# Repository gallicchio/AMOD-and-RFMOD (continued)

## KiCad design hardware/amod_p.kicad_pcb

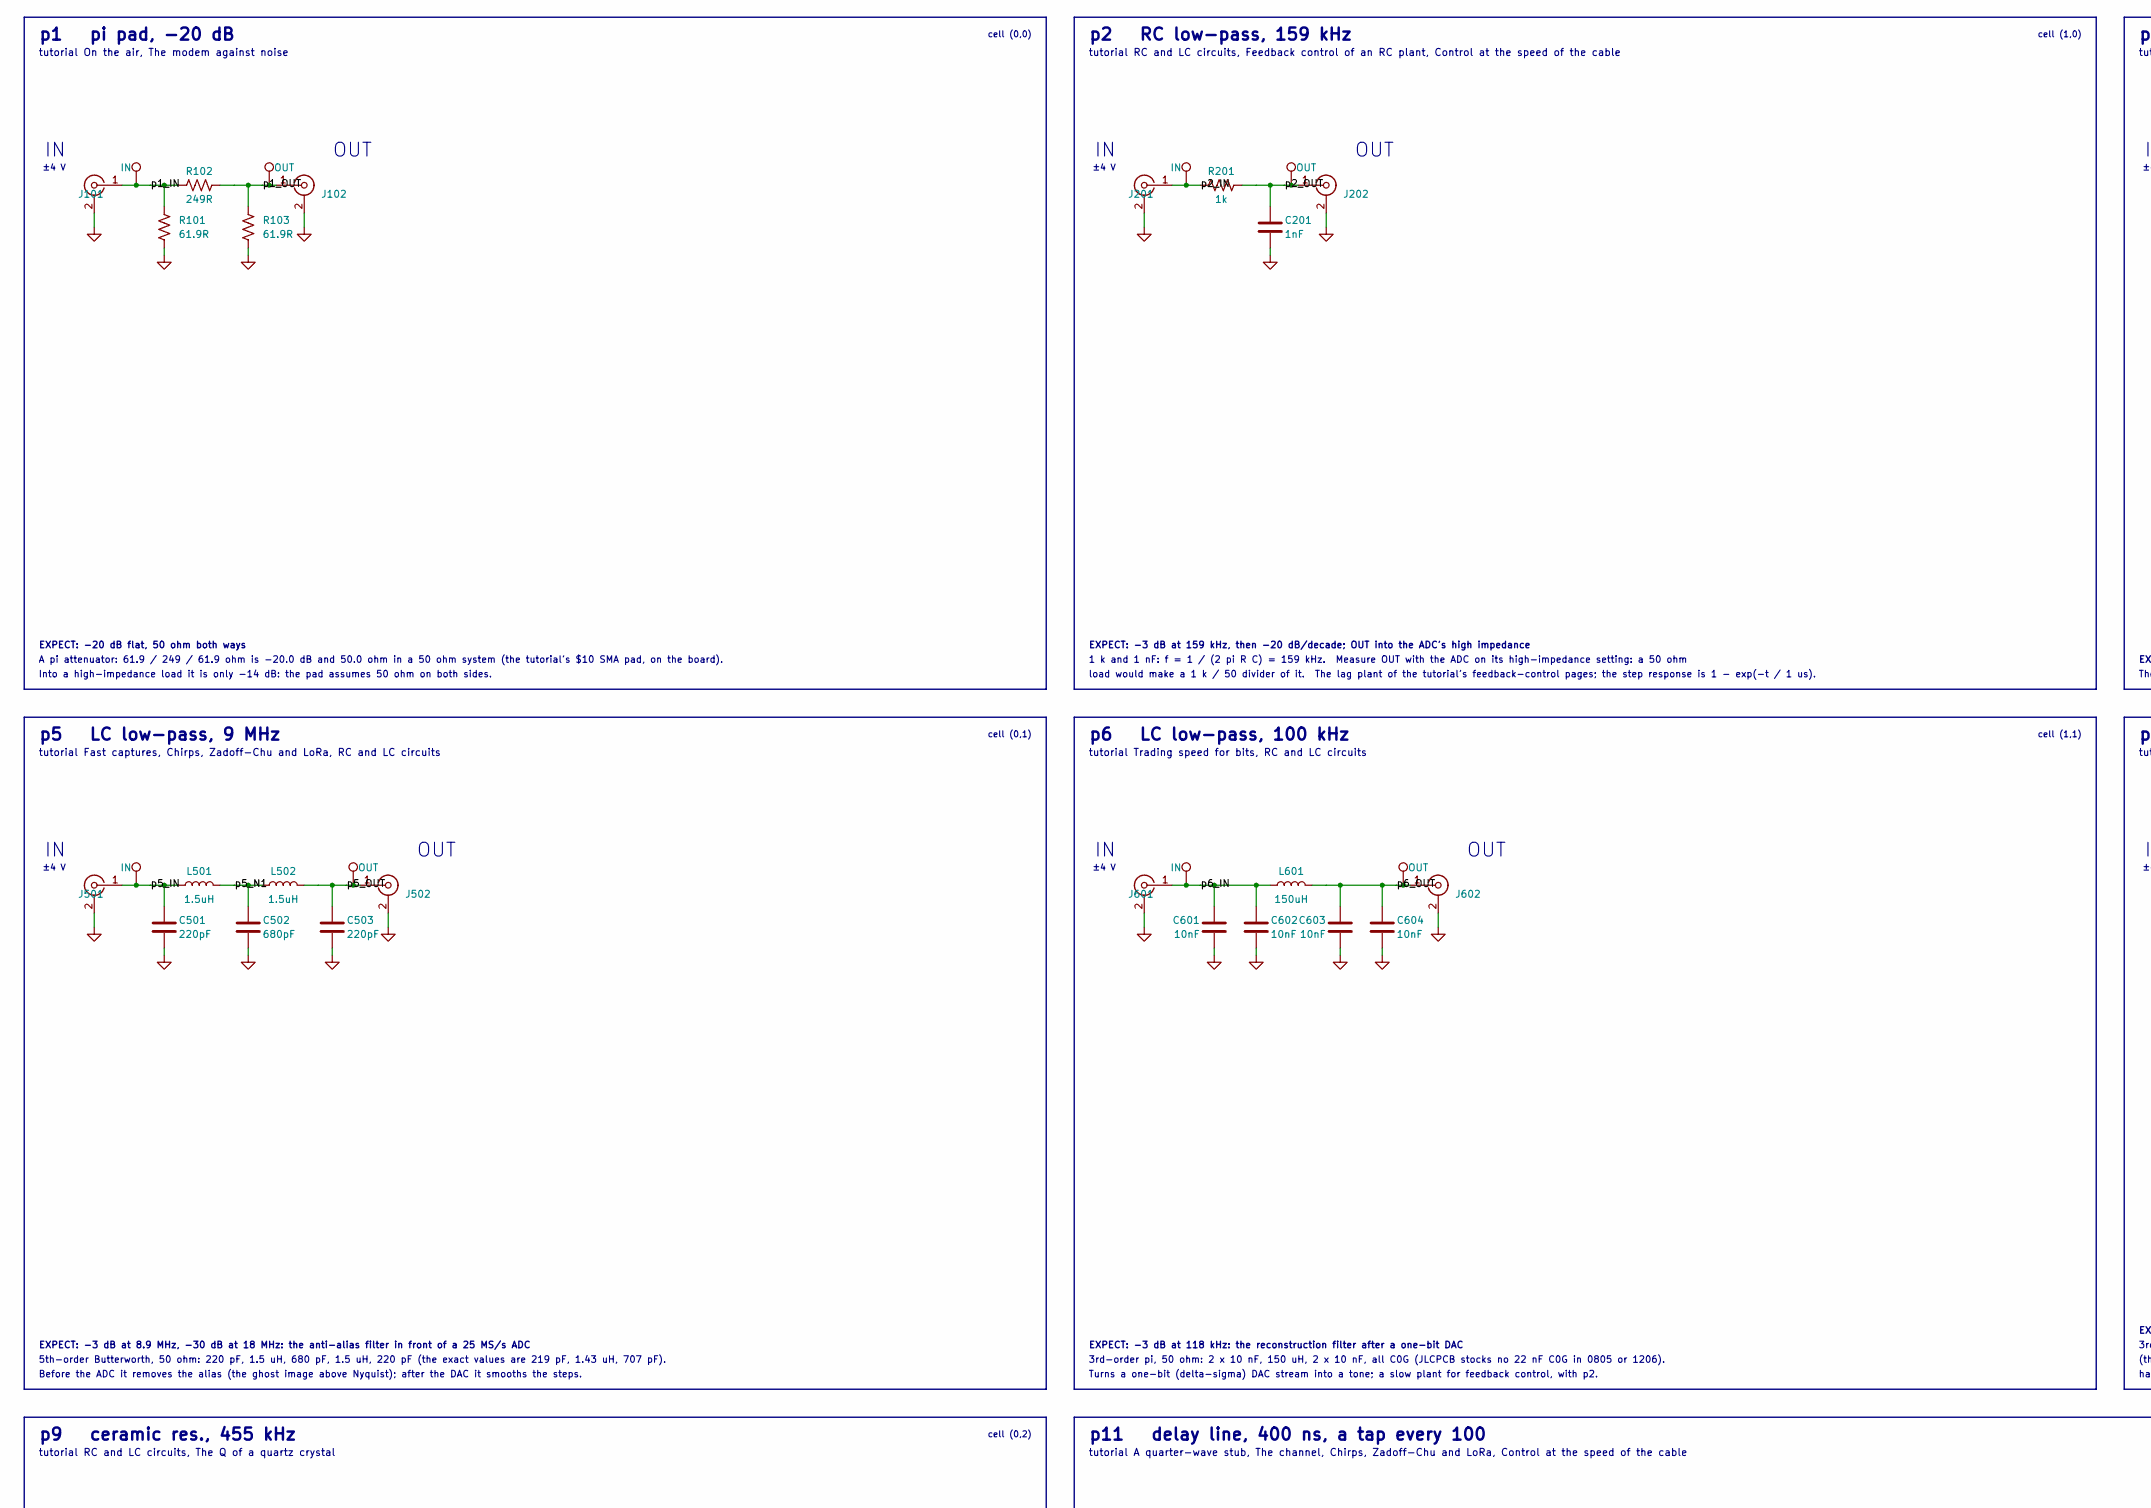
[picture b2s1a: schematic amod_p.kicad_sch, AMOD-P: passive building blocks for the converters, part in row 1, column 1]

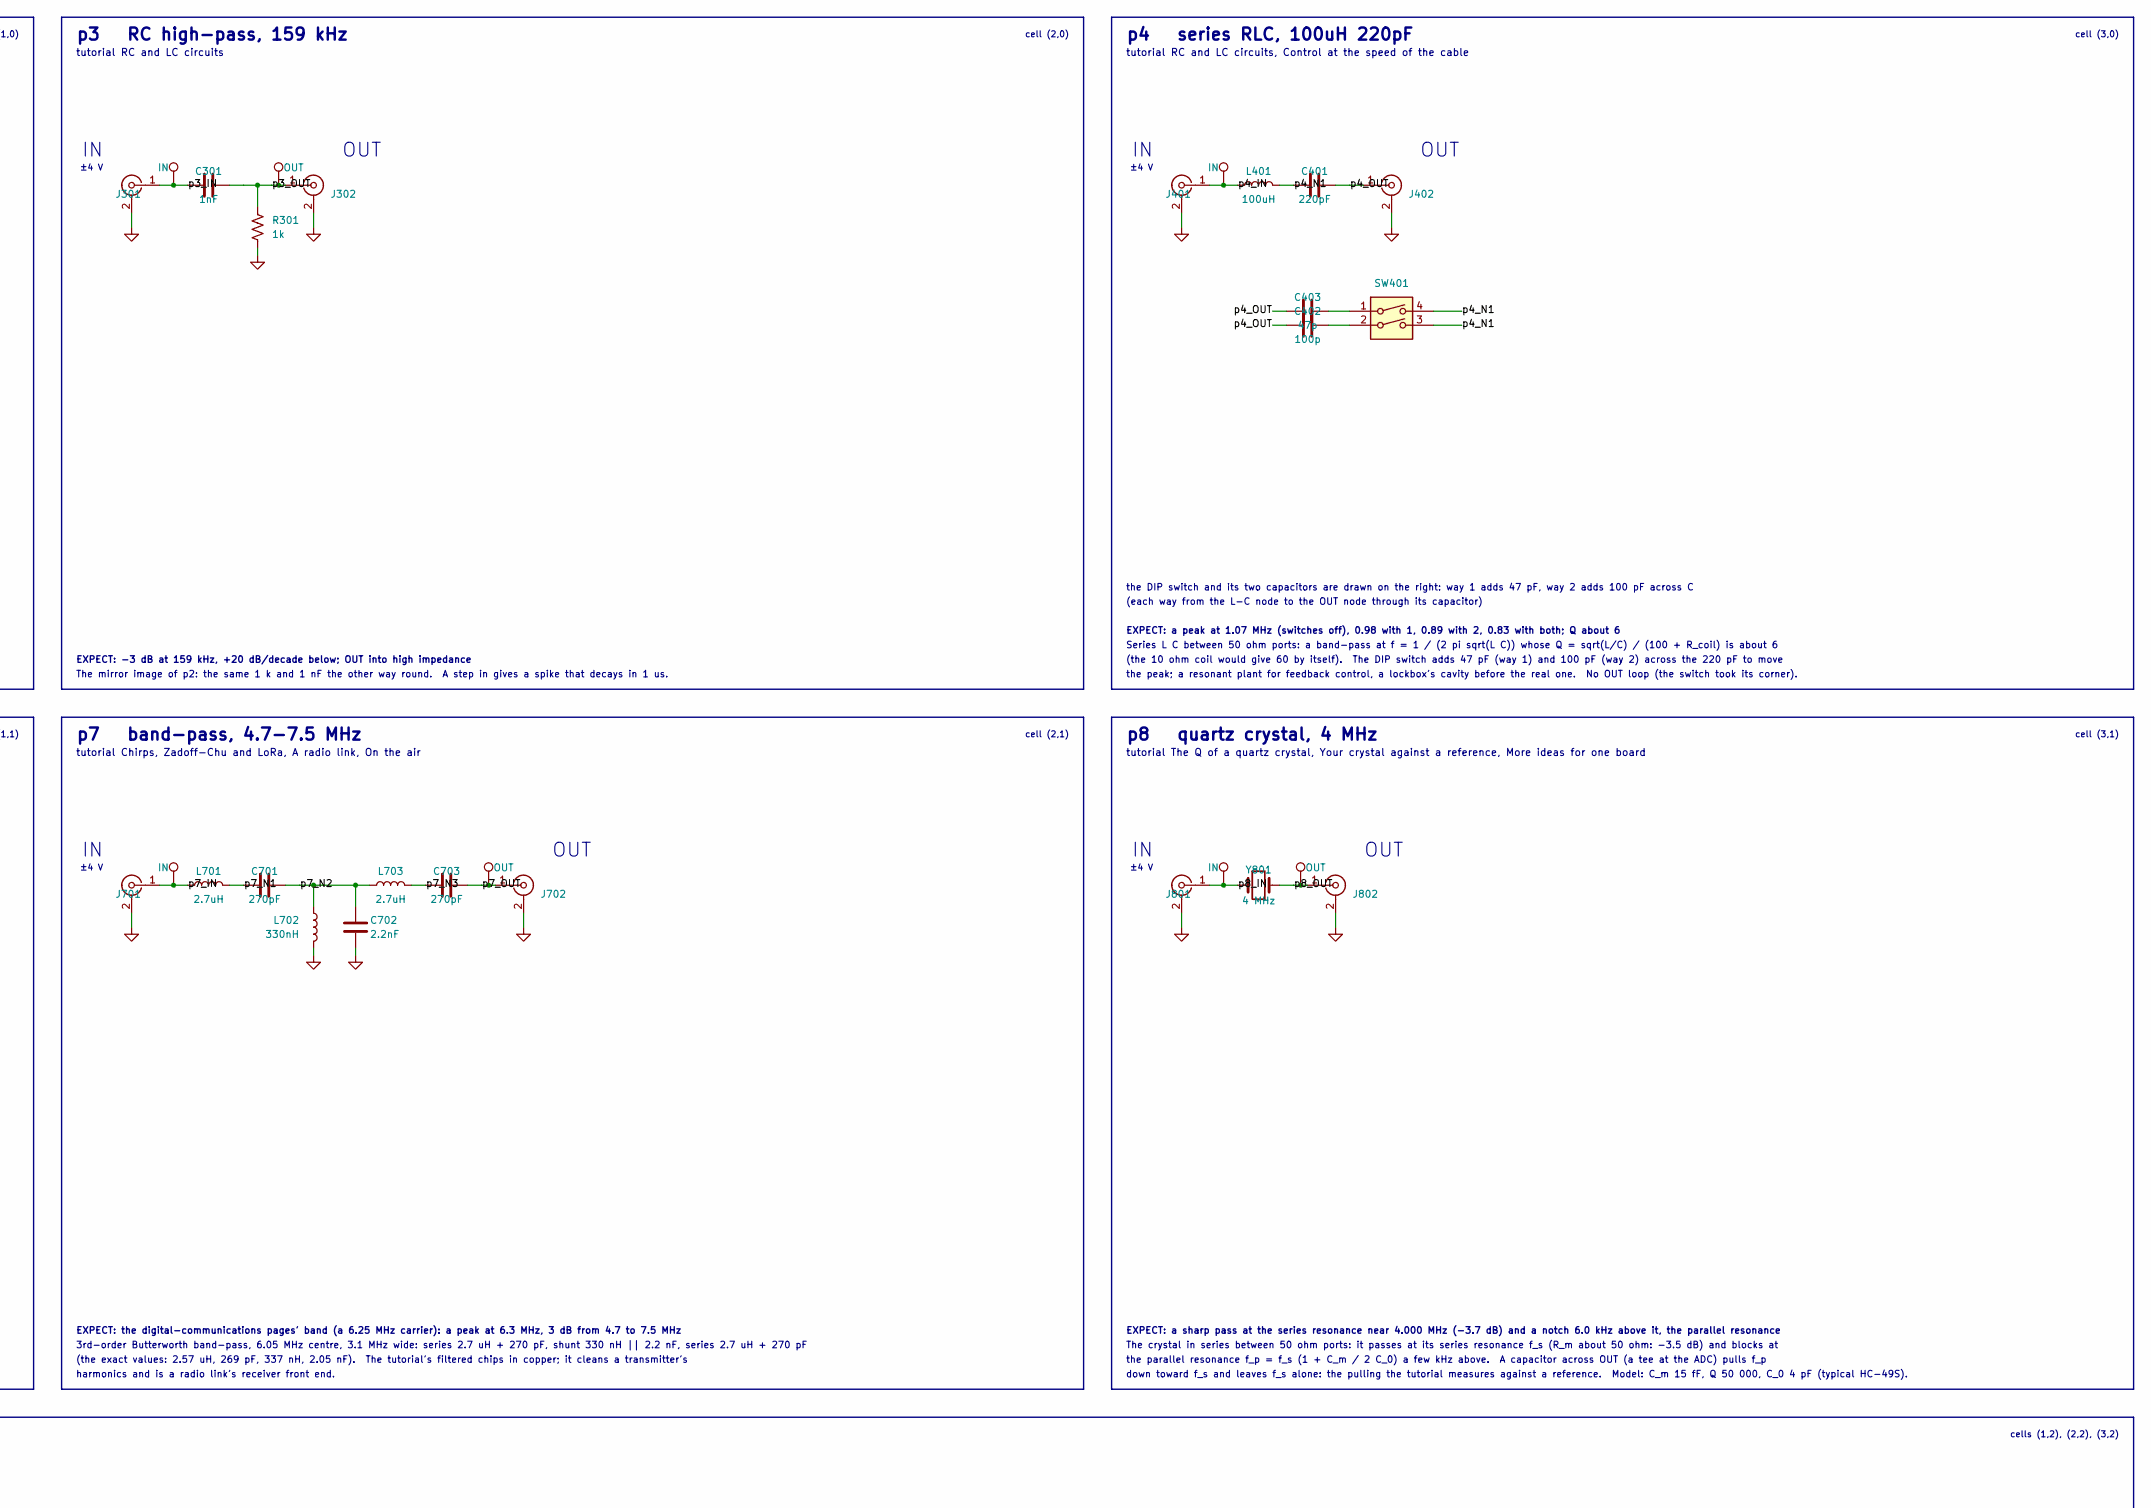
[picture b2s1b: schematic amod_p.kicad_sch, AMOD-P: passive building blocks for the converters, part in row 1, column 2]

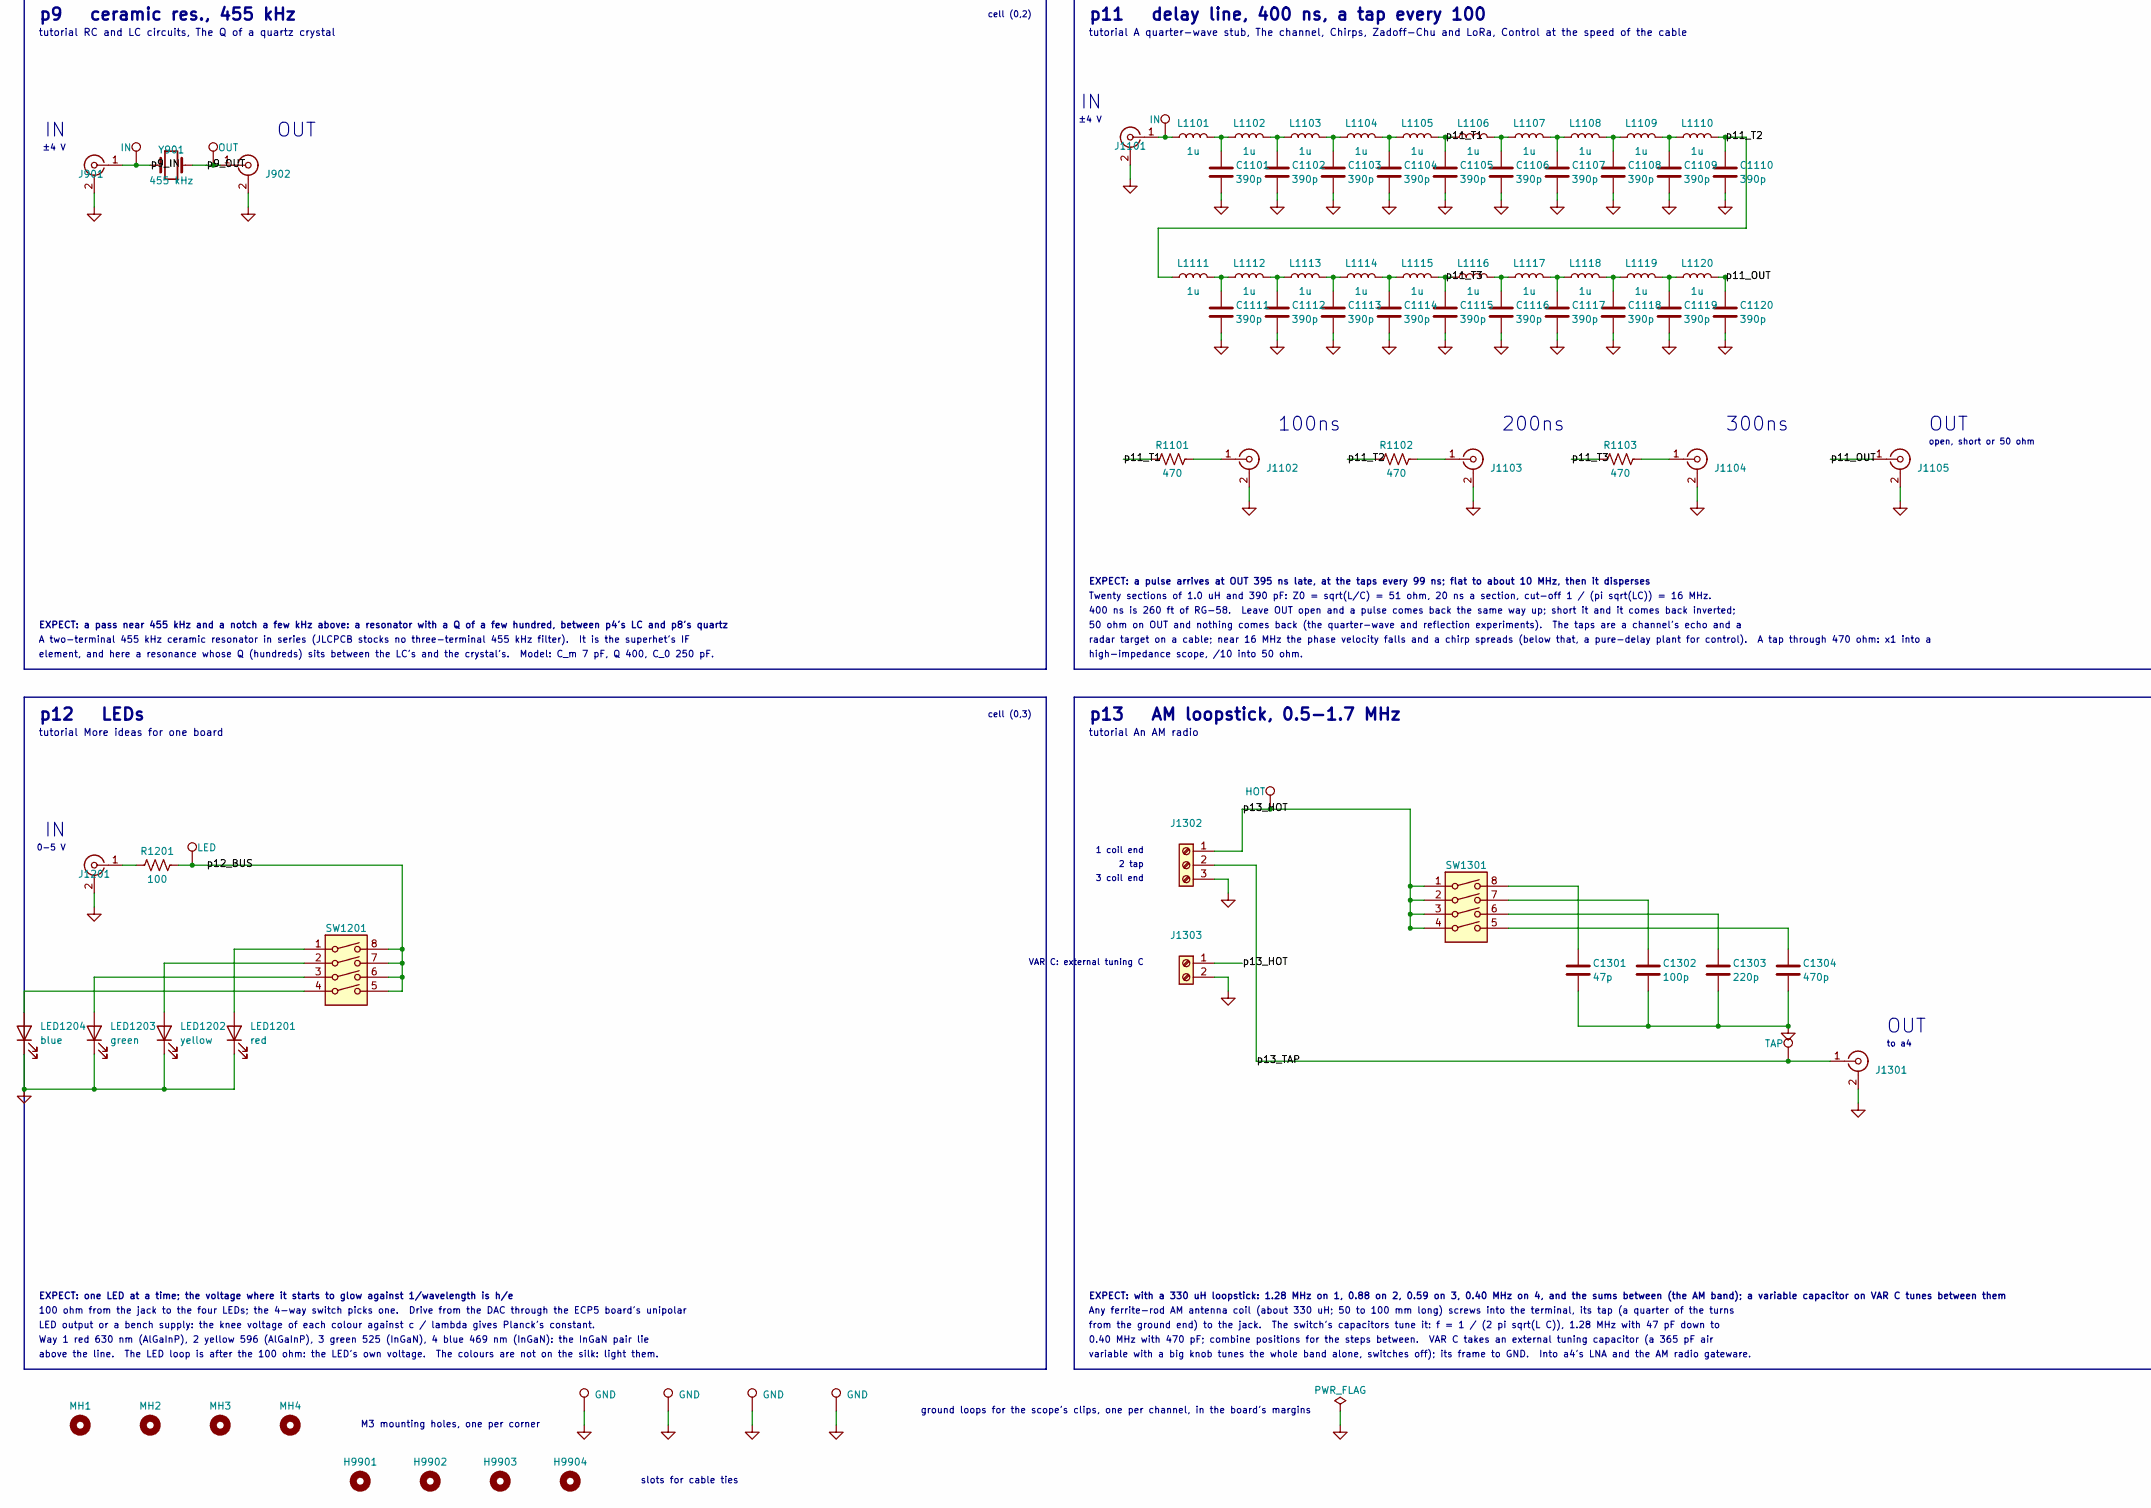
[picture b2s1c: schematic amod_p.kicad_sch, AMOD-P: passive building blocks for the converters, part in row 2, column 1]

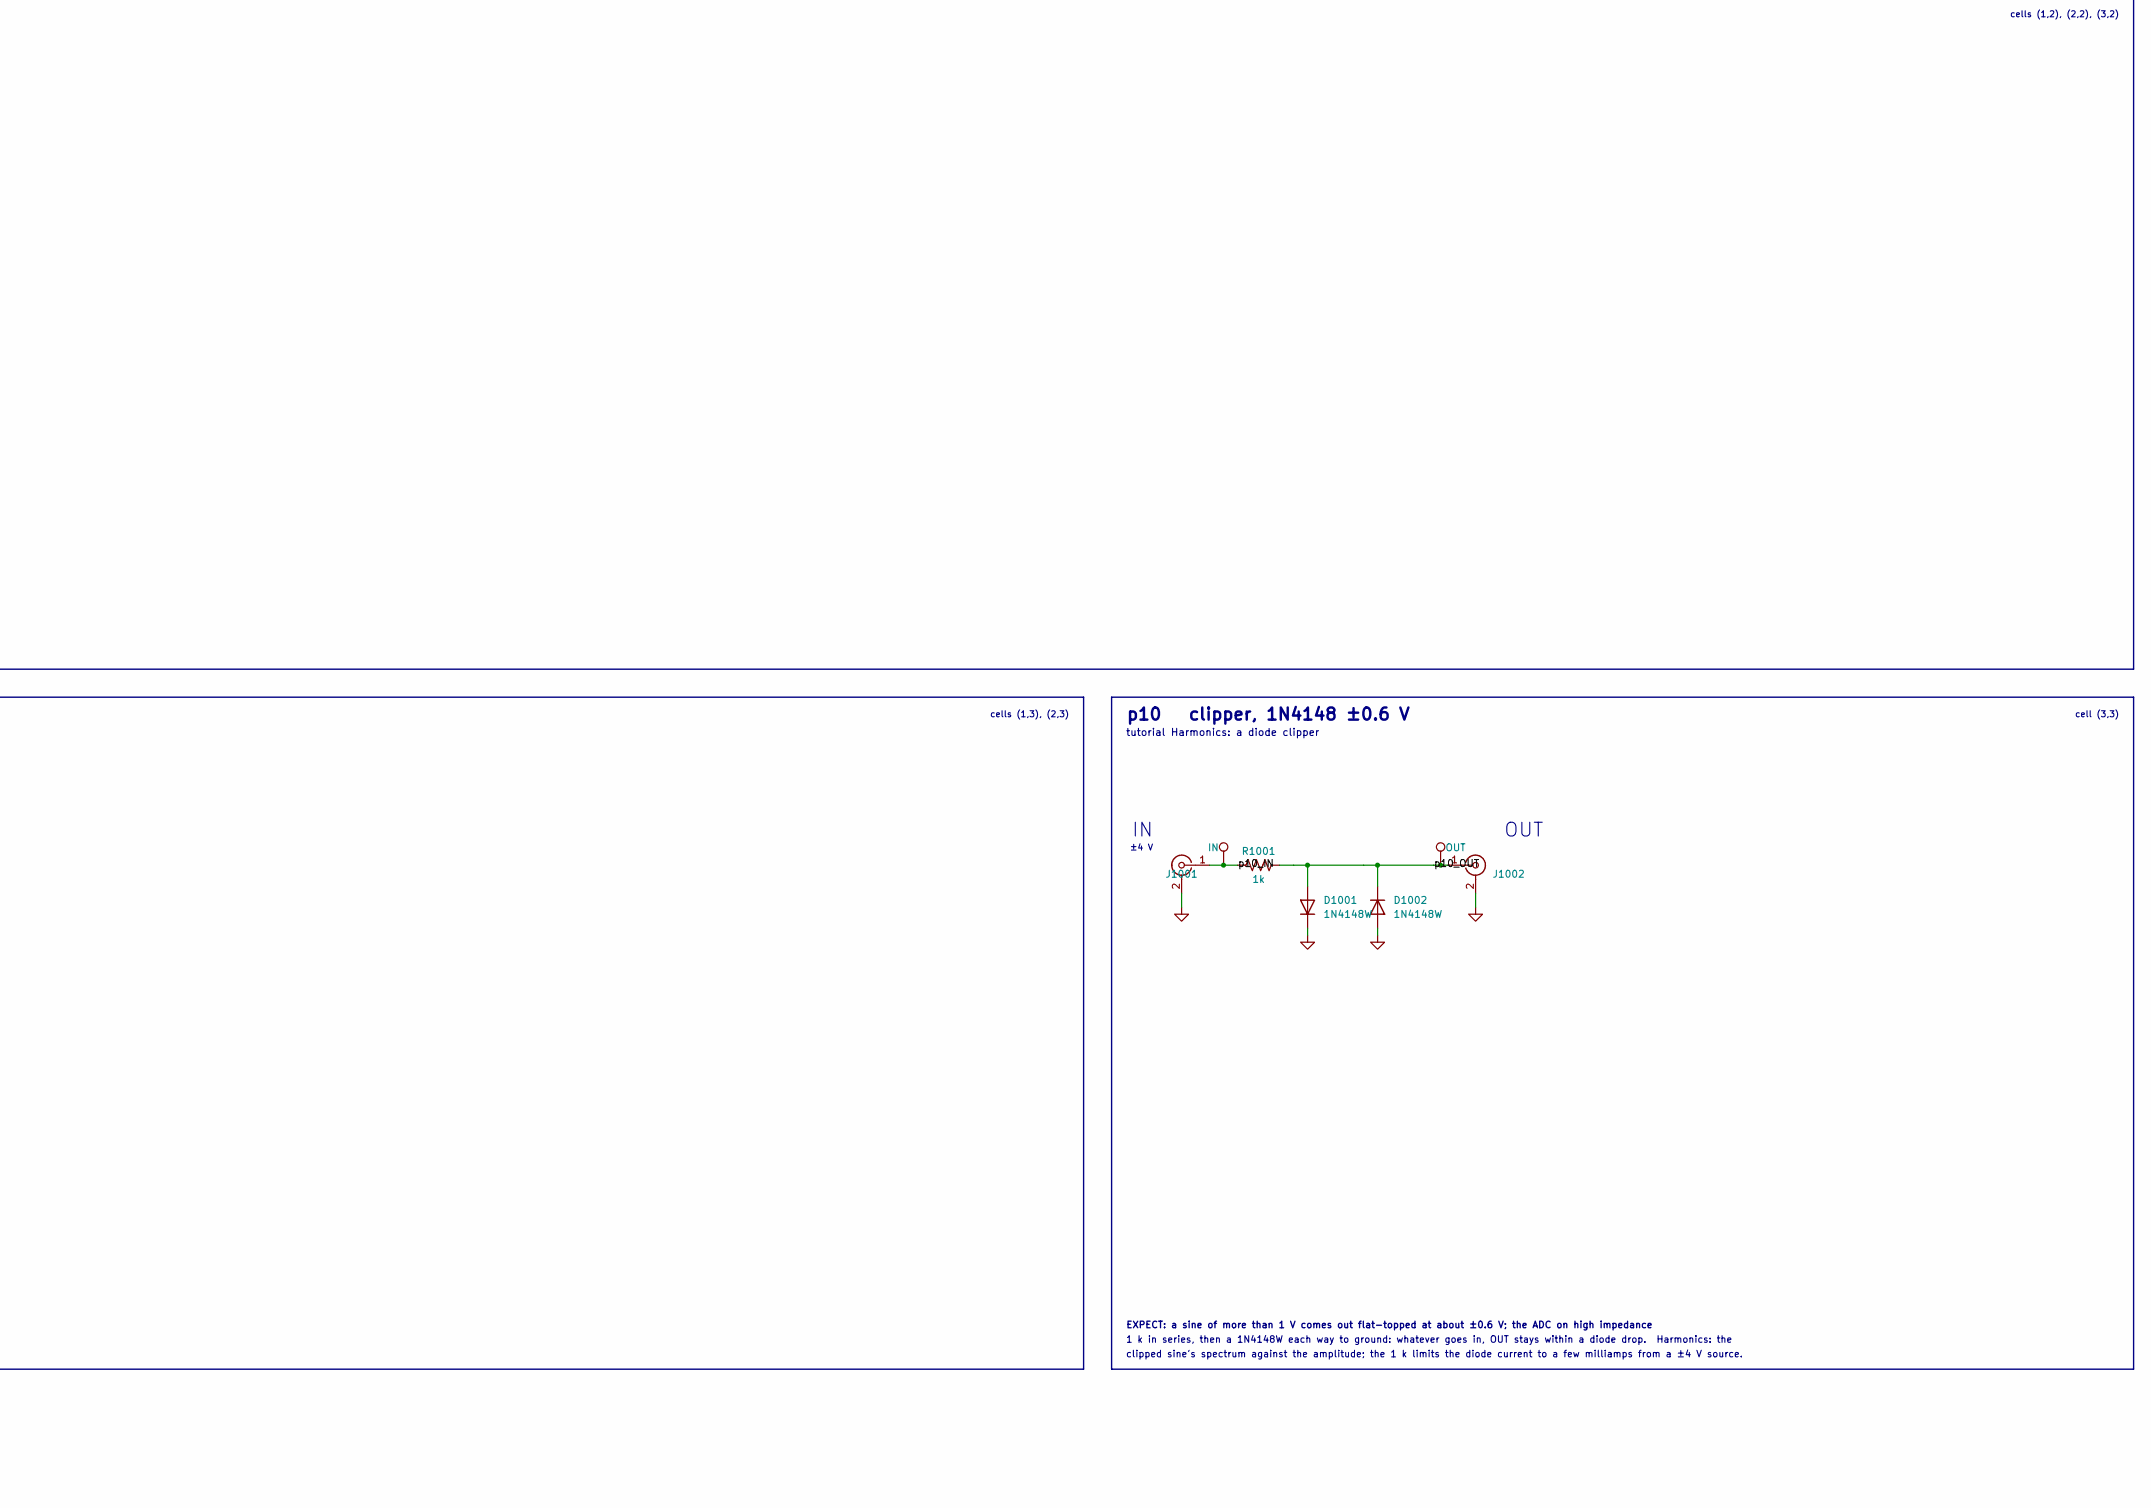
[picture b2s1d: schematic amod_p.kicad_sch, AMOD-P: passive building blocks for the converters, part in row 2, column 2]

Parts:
C201, C301: 1nF; C_0805_2012Metric; MPN 0805CG102J500NT; LCSC C29925
C401, C501, C503: 220pF; C_0805_2012Metric; MPN 0805CG221J500NT; LCSC C1805
C402: 100p; C_0603_1608Metric; MPN CL10C101JB8NNNC; LCSC C14858
C403: 47p; C_0603_1608Metric; MPN CL10C470JB8NNNC; LCSC C1671
C502: 680pF; C_0805_2012Metric; MPN 0805CG681J500NT; LCSC C1835
C601, C602, C603, C604: 10nF; C_0805_2012Metric; MPN 0805CG103J500NT; LCSC C2971995
C701, C703: 270pF; C_0603_1608Metric; MPN 0603CG271J500NT; LCSC C501846
C702: 2.2nF; C_0603_1608Metric; MPN 0603CG222J500NT; LCSC C2991172
C1101, C1102, C1103, C1104, C1105, C1106, C1107, C1108, C1109, C1110, C1111, C1112, C1113, C1114, C1115, C1116, C1117, C1118, C1119, C1120: 390p; C_0402_1005Metric; MPN CC0402JRNPO9BN391; LCSC C282239
C1301: 47p; C_0805_2012Metric; MPN CL21C470JBANNNC; LCSC C14857
C1302: 100p; C_0805_2012Metric; MPN CL21C101JBANNNC; LCSC C1790
C1303: 220p; C_0805_2012Metric; MPN 0805CG221J500NT; LCSC C1805
C1304: 470p; C_0805_2012Metric; MPN 0805CG471J500NT; LCSC C1822
D1001, D1002: 1N4148W; D_SOD-123; MPN 1N4148W; LCSC C81598
H9901, H9902, H9903, H9904: slot; Slot_CableTie_1.2x3.4mm
J101, J102, J201, J202, J301, J302, J401, J402, J501, J502, J601, J602, J701, J702, J801, J802, J901, J902, J1001, J1002, J1101, J1102, J1103, J1104, J1105, J1201, J1301: SMA; SMA_BWSMA-KE-Z001_Vertical; MPN BWSMA-KE-Z001; LCSC C496549
J1302: coil; TerminalBlock_KF301_1x03_P5.00mm; MPN KF301-5.0-3P; LCSC C474882
J1303: VAR C; TerminalBlock_KF301_1x02_P5.00mm; MPN KF301-5.0-2P; LCSC C474881
L401: 100uH; L_1210_3225Metric; MPN NLV32T-101J-PF; LCSC C76836
L501, L502: 1.5uH; L_0805_2012Metric; MPN SDFL2012Q1R5KTF; LCSC C316402
L601: 150uH; L_1210_3225Metric; MPN NLCV32T-151K-EF; LCSC C250237
L701, L703: 2.7uH; L_0603_1608Metric; MPN SDFL1608Q2R7KTF; LCSC C29946
L702: 330nH; L_0603_1608Metric; MPN CS0603-R33J-S; LCSC C142165
L1101, L1102, L1103, L1104, L1105, L1106, L1107, L1108, L1109, L1110, L1111, L1112, L1113, L1114, L1115, L1116, L1117, L1118, L1119, L1120: 1u; L_0603_1608Metric; MPN SDFL1608Q1R0KTF; LCSC C22037
LED1201: red; LED_0805_2012Metric_Kbar; MPN NCD0805R1; LCSC C84256
LED1202: yellow; LED_0805_2012Metric_Kbar; MPN KT-0805Y; LCSC C2296
LED1203: green; LED_0805_2012Metric_Kbar; MPN KT-0805G; LCSC C2297
LED1204: blue; LED_0805_2012Metric_Kbar; MPN KT-0805B; LCSC C2293
MH1, MH2, MH3, MH4: MountingHole; MountingHole_3.2mm_M3
R101, R103: 61.9R; R_0805_2012Metric; MPN 0805W8F619JT5E; LCSC C17779
R102: 249R; R_0805_2012Metric; MPN 0805W8F2490T5E; LCSC C32281
R201, R301, R1001: 1k; R_0805_2012Metric; MPN 0805W8F1001T5E; LCSC C17513
R1101, R1102, R1103: 470; R_0805_2012Metric; MPN 0805W8F4700T5E; LCSC C17710
R1201: 100; R_0805_2012Metric; MPN 0805W8F1000T5E; LCSC C17408
SW401: DIP2; SW_DIP_SPSTx02_Slide_1.27mm_DSHP02; MPN DSHP02TSGET; LCSC C40735
SW1201, SW1301: DIP4; SW_DIP_SPSTx04_Slide_1.27mm_DSHP04; MPN DSHP04TSGET; LCSC C40736
TP101, TP201, TP301, TP401, TP501, TP601, TP701, TP801, TP901, TP1001, TP1101: IN; TestPoint_Loop_RH-5019; MPN RH-5019; LCSC C5199800
TP102, TP202, TP302, TP502, TP602, TP702, TP802, TP902, TP1002: OUT; TestPoint_Loop_RH-5019; MPN RH-5019; LCSC C5199800
TP1201: LED; TestPoint_Loop_RH-5019; MPN RH-5019; LCSC C5199800
TP1301: TAP; TestPoint_Loop_RH-5019; MPN RH-5019; LCSC C5199800
TP1302: HOT; TestPoint_Loop_RH-5019; MPN RH-5019; LCSC C5199800
TP9901, TP9902, TP9903, TP9904: GND; TestPoint_Loop_RH-5019; MPN RH-5019; LCSC C5199800
Y801: 4 MHz; Crystal_HC49-S_SMD; MPN X49SM4MSD2SC; LCSC C13774
Y901: 455 kHz; Resonator_Ceramic_2Pin_P5.00mm_KCR455E; MPN KCR455E; LCSC C366989

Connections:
/p1_IN: J101.1 (In), R101.1, R102.1, TP101.1
/p1_OUT: J102.1 (In), R102.2, R103.1, TP102.1
/p2_IN: J201.1 (In), R201.1, TP201.1
/p2_OUT: C201.1, J202.1 (In), R201.2, TP202.1
/p3_IN: C301.1, J301.1 (In), TP301.1
/p3_OUT: C301.2, J302.1 (In), R301.1, TP302.1
/p4_IN: J401.1 (In), L401.1, TP401.1
/p4_N1: C401.1, L401.2, SW401.3, SW401.4
/p4_OUT: C401.2, C402.2, C403.2, J402.1 (In)
/p5_IN: C501.1, J501.1 (In), L501.1, TP501.1
/p5_N1: C502.1, L501.2, L502.1
/p5_OUT: C503.1, J502.1 (In), L502.2, TP502.1
/p6_IN: C601.1, C602.1, J601.1 (In), L601.1, TP601.1
/p6_OUT: C603.1, C604.1, J602.1 (In), L601.2, TP602.1
/p7_IN: J701.1 (In), L701.1, TP701.1
/p7_N1: C701.1, L701.2
/p7_N2: C701.2, C702.1, L702.1, L703.1
/p7_N3: C703.1, L703.2
/p7_OUT: C703.2, J702.1 (In), TP702.1
/p8_IN: J801.1 (In), TP801.1, Y801.1
/p8_OUT: J802.1 (In), TP802.1, Y801.2
/p9_IN: J901.1 (In), TP901.1, Y901.1
/p9_OUT: J902.1 (In), TP902.1, Y901.2
/p10_IN: J1001.1 (In), R1001.1, TP1001.1
/p10_OUT: D1001.2 (A), D1002.1 (K), J1002.1 (In), R1001.2, TP1002.1
/p11_OUT: C1120.1, J1105.1 (In), L1120.2
/p11_T1: C1105.1, L1105.2, L1106.1, R1101.1
/p11_T2: C1110.1, L1110.2, L1111.1, R1102.1
/p11_T3: C1115.1, L1115.2, L1116.1, R1103.1
/p12_BUS: R1201.2, SW1201.5, SW1201.6, SW1201.7, SW1201.8, TP1201.1
/p13_HOT: J1302.1, J1303.1, SW1301.1, SW1301.2, SW1301.3, SW1301.4, TP1302.1
/p13_TAP: J1301.1 (In), J1302.2, TP1301.1
GND: C201.2, C501.2, C502.2, C503.2, C601.2, C602.2, C603.2, C604.2, C702.2, C1101.2, C1102.2, C1103.2, C1104.2, C1105.2, C1106.2, C1107.2, C1108.2, C1109.2, C1110.2, C1111.2, C1112.2, C1113.2, C1114.2, C1115.2, C1116.2, C1117.2, C1118.2, C1119.2, C1120.2, C1301.2, C1302.2, C1303.2, C1304.2, D1001.1 (K), D1002.2 (A), J101.2 (Ext), J102.2 (Ext), J201.2 (Ext), J202.2 (Ext), J301.2 (Ext), J302.2 (Ext), J401.2 (Ext), J402.2 (Ext), J501.2 (Ext), J502.2 (Ext), J601.2 (Ext), J602.2 (Ext), J701.2 (Ext), J702.2 (Ext), J801.2 (Ext), J802.2 (Ext), J901.2 (Ext), J902.2 (Ext), J1001.2 (Ext), J1002.2 (Ext), J1101.2 (Ext), J1102.2 (Ext), J1103.2 (Ext), J1104.2 (Ext), J1105.2 (Ext), J1201.2 (Ext), J1301.2 (Ext), J1302.3, J1303.2, L702.2, LED1201.1 (K), LED1202.1 (K), LED1203.1 (K), LED1204.1 (K), R101.2, R103.2, R301.2, TP9901.1, TP9902.1, TP9903.1, TP9904.1
unnamed: C402.1, SW401.2
unnamed: C403.1, SW401.1
unnamed: C1101.1, L1101.2, L1102.1
unnamed: C1102.1, L1102.2, L1103.1
unnamed: C1103.1, L1103.2, L1104.1
unnamed: C1104.1, L1104.2, L1105.1
unnamed: C1106.1, L1106.2, L1107.1
unnamed: C1107.1, L1107.2, L1108.1
unnamed: C1108.1, L1108.2, L1109.1
unnamed: C1109.1, L1109.2, L1110.1
unnamed: C1111.1, L1111.2, L1112.1
unnamed: C1112.1, L1112.2, L1113.1
unnamed: C1113.1, L1113.2, L1114.1
unnamed: C1114.1, L1114.2, L1115.1
unnamed: C1116.1, L1116.2, L1117.1
unnamed: C1117.1, L1117.2, L1118.1
unnamed: C1118.1, L1118.2, L1119.1
unnamed: C1119.1, L1119.2, L1120.1
unnamed: C1301.1, SW1301.8
unnamed: C1302.1, SW1301.7
unnamed: C1303.1, SW1301.6
unnamed: C1304.1, SW1301.5
unnamed: J1101.1 (In), L1101.1, TP1101.1
unnamed: J1102.1 (In), R1101.2
unnamed: J1103.1 (In), R1102.2
unnamed: J1104.1 (In), R1103.2
unnamed: J1201.1 (In), R1201.1
unnamed: LED1201.2 (A), SW1201.1
unnamed: LED1202.2 (A), SW1201.2
unnamed: LED1203.2 (A), SW1201.3
unnamed: LED1204.2 (A), SW1201.4

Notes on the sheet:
1 k in series, then a 1N4148W each way to ground: whatever goes in, OUT stays within a diode drop. Harmonics: the
±4 V
the peak; a resonant plant for feedback control, a lockbox's cavity before the real one. No OUT loop (the switch took its corner).
50 ohm on OUT and nothing comes back (the quarter-wave and reflection experiments). The taps are a channel's echo and a
p10 clipper, 1N4148 ±0.6 V
Series L C between 50 ohm ports: a band-pass at f = 1 / (2 pi sqrt(L C)) whose Q = sqrt(L/C) / (100 + R_coil) is about 6
EXPECT: -3 dB at 159 kHz, then -20 dB/decade; OUT into the ADC's high impedance
p8 quartz crystal, 4 MHz
cell (2,1)
EXPECT: -20 dB flat, 50 ohm both ways
2 tap
100 ohm from the jack to the four LEDs; the 4-way switch picks one. Drive from the DAC through the ECP5 board's unipolar
EXPECT: with a 330 uH loopstick: 1.28 MHz on 1, 0.88 on 2, 0.59 on 3, 0.40 MHz on 4, and the sums between (the AM band); a variable capacitor on VAR C tunes between them
cell (0,2)
EXPECT: -3 dB at 8.9 MHz, -30 dB at 18 MHz: the anti-alias filter in front of a 25 MS/s ADC
The mirror image of p2: the same 1 k and 1 nF the other way round. A step in gives a spike that decays in 1 us.
clipped sine's spectrum against the amplitude; the 1 k limits the diode current to a few milliamps from a ±4 V source.
cell (2,0)
(the exact values: 2.57 uH, 269 pF, 337 nH, 2.05 nF). The tutorial's filtered chips in copper; it cleans a transmitter's
p11 delay line, 400 ns, a tap every 100
p13 AM loopstick, 0.5-1.7 MHz
cell (3,3)
400 ns is 260 ft of RG-58. Leave OUT open and a pulse comes back the same way up; short it and it comes back inverted;
cells (1,3), (2,3)
p4 series RLC, 100uH 220pF
EXPECT: -3 dB at 118 kHz: the reconstruction filter after a one-bit DAC
above the line. The LED loop is after the 100 ohm: the LED's own voltage. The colours are not on the silk: light them.
3rd-order Butterworth band-pass, 6.05 MHz centre, 3.1 MHz wide: series 2.7 uH + 270 pF, shunt 330 nH || 2.2 nF, series 2.7 uH + 270 pF
p9 ceramic res., 455 kHz
p12 LEDs
p6 LC low-pass, 100 kHz
slots for cable ties
p2 RC low-pass, 159 kHz
200ns
cell (0,1)
EXPECT: a sine of more than 1 V comes out flat-topped at about ±0.6 V; the ADC on high impedance
(the 10 ohm coil would give 60 by itself). The DIP switch adds 47 pF (way 1) and 100 pF (way 2) across the 220 pF to move
radar target on a cable; near 16 MHz the phase velocity falls and a chirp spreads (below that, a pure-delay plant for control). A tap through 470 ohm: x1 into a
cells (1,2), (2,2), (3,2)
cell (0,3)

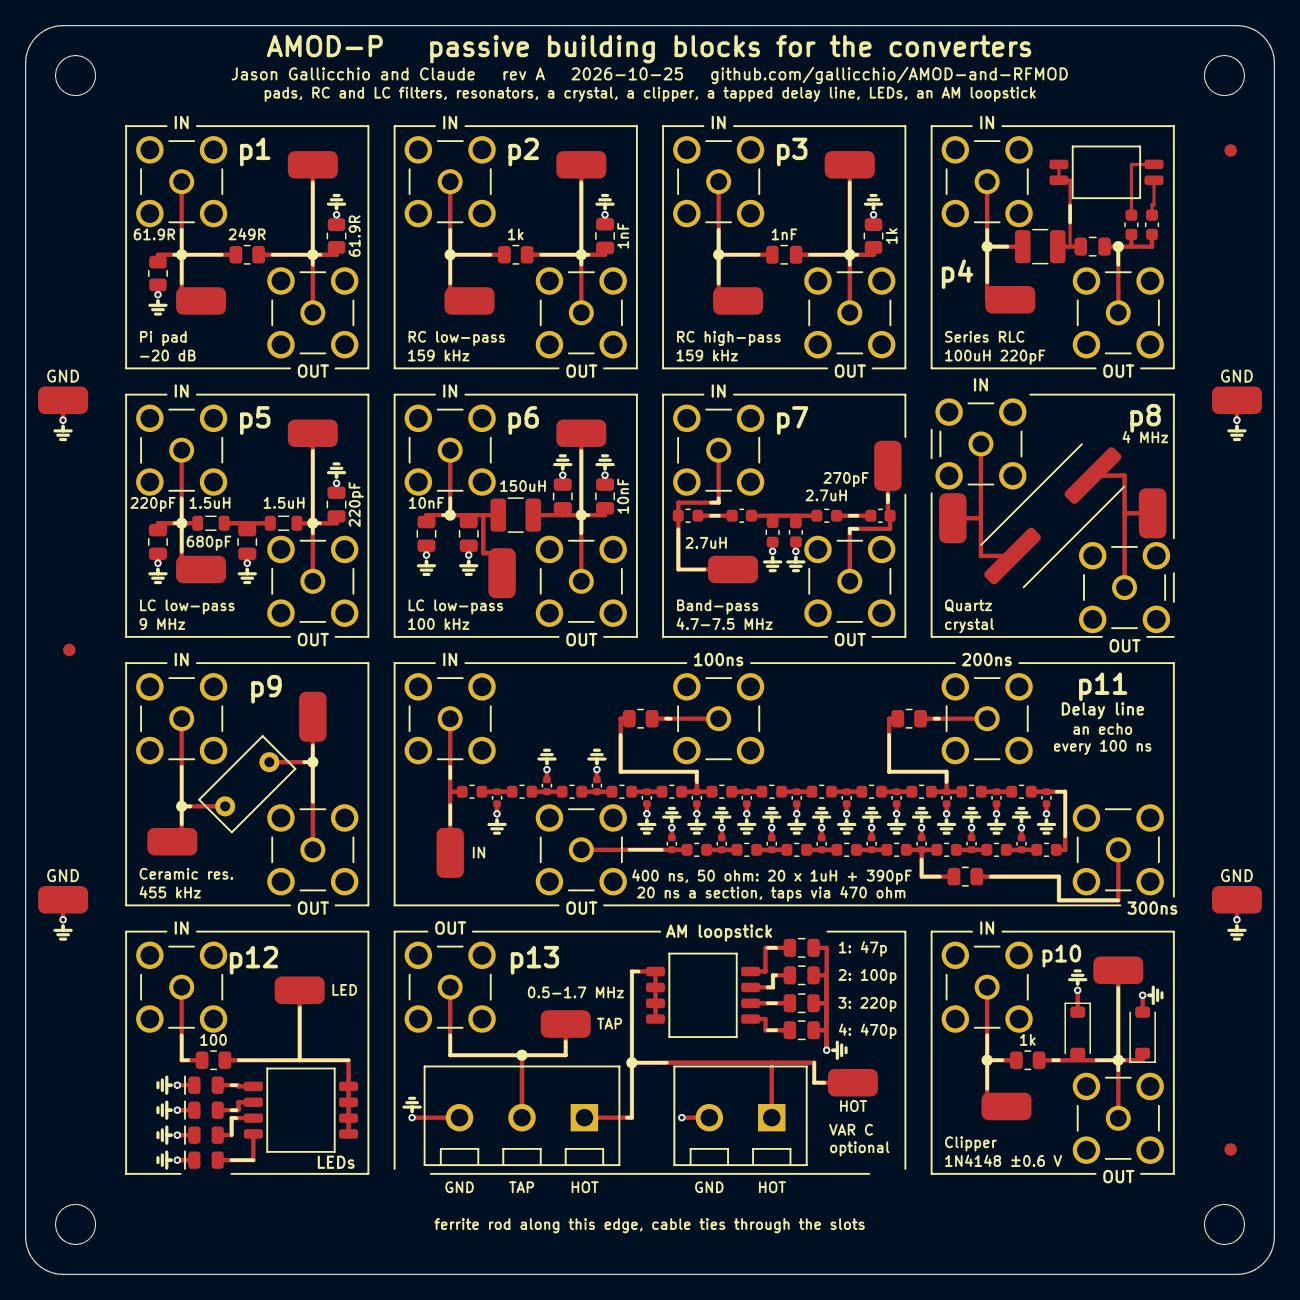
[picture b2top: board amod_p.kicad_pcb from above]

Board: 2 copper layers, 100.0 x 100.0 mm, 151 parts (0 on the bottom side), 64 nets.

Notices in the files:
hardware/amod_p.kicad_sch:
Board: Jason Gallicchio and Claude  |  open hardware, CERN-OHL-P-2.0  |  github.com/gallicchio/AMOD-and-RFMOD
